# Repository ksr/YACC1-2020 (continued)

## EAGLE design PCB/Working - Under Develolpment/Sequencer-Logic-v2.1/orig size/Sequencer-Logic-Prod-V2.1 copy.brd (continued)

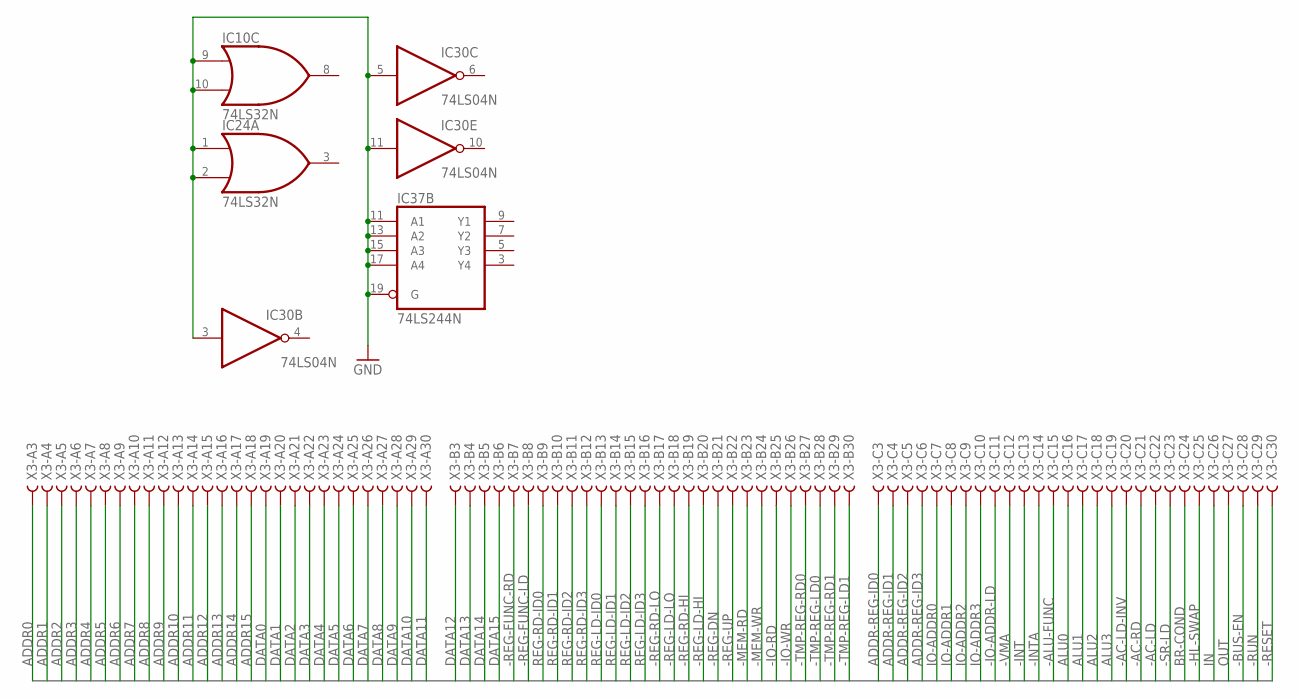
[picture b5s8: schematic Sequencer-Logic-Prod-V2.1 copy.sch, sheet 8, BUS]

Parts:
IC10, IC24: 74LS32N; DIL14
IC30: 74LS04N; DIL14
IC37: 74LS244N; DIL20
X3: FABC96R

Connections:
-AC-LD: X3.C22; also elsewhere on the board
-AC-LD-INV: X3.C20; also elsewhere on the board
-AC-RD: X3.C21; also elsewhere on the board
-ALU-FUNC: X3.C15; also elsewhere on the board
-BUS-EN: X3.C28; also elsewhere on the board
-HL-SWAP: X3.C25; also elsewhere on the board
-INT: X3.C13; also elsewhere on the board
-INTA: X3.C14; also elsewhere on the board
-IO-ADDR-LD: X3.C11; also elsewhere on the board
-IO-RD: X3.B25; also elsewhere on the board
-IO-WR: X3.B26; also elsewhere on the board
-MEM-RD: X3.B23; also elsewhere on the board
-MEM-WR: X3.B24; also elsewhere on the board
-REG-DN: X3.B21; also elsewhere on the board
-REG-FUNC-LD: X3.B8; also elsewhere on the board
-REG-FUNC-RD: X3.B7; also elsewhere on the board
-REG-LD-HI: X3.B20; also elsewhere on the board
-REG-LD-LO: X3.B18; also elsewhere on the board
-REG-RD-HI: X3.B19; also elsewhere on the board
-REG-RD-LO: X3.B17; also elsewhere on the board
-REG-UP: X3.B22; also elsewhere on the board
-RESET: X3.C30; also elsewhere on the board
-RUN: X3.C29
-SR-LD: X3.C23; also elsewhere on the board
-TMP-REG-LD0: X3.B28; also elsewhere on the board
-TMP-REG-LD1: X3.B30; also elsewhere on the board
-TMP-REG-RD0: X3.B27; also elsewhere on the board
-TMP-REG-RD1: X3.B29; also elsewhere on the board
-VMA: X3.C12; also elsewhere on the board
ADDR0: X3.A3
ADDR1: X3.A4
ADDR2: X3.A5
ADDR3: X3.A6
ADDR4: X3.A7
ADDR5: X3.A8
ADDR6: X3.A9
ADDR7: X3.A10
ADDR8: X3.A11
ADDR9: X3.A12
ADDR10: X3.A13
ADDR11: X3.A14
ADDR12: X3.A15
ADDR13: X3.A16
ADDR14: X3.A17
ADDR15: X3.A18
ADDR-REG-ID0: X3.C3; also elsewhere on the board
ADDR-REG-ID1: X3.C4; also elsewhere on the board
ADDR-REG-ID2: X3.C5; also elsewhere on the board
ADDR-REG-ID3: X3.C6; also elsewhere on the board
ALU0: X3.C16; also elsewhere on the board
ALU1: X3.C17; also elsewhere on the board
ALU2: X3.C18; also elsewhere on the board
ALU3: X3.C19; also elsewhere on the board
BR-COND: X3.C24; also elsewhere on the board
DATA0: X3.A19; also elsewhere on the board
DATA1: X3.A20; also elsewhere on the board
DATA2: X3.A21; also elsewhere on the board
DATA3: X3.A22; also elsewhere on the board
DATA4: X3.A23; also elsewhere on the board
DATA5: X3.A24; also elsewhere on the board
DATA6: X3.A25; also elsewhere on the board
DATA7: X3.A26; also elsewhere on the board
DATA8: X3.A27; also elsewhere on the board
DATA9: X3.A28; also elsewhere on the board
DATA10: X3.A29; also elsewhere on the board
DATA11: X3.A30; also elsewhere on the board
DATA12: X3.B3; also elsewhere on the board
DATA13: X3.B4; also elsewhere on the board
DATA14: X3.B5; also elsewhere on the board
DATA15: X3.B6; also elsewhere on the board
GND: IC10.7 (GND), IC10.9 (I0), IC10.10 (I1), IC24.1 (I0), IC24.2 (I1), IC24.7 (GND), IC30.3 (I), IC30.5 (I), IC30.7 (GND), IC30.11 (I), IC37.10 (GND), IC37.11 (A1), IC37.13 (A2), IC37.15 (A3), IC37.17 (A4), IC37.19 (G); also elsewhere on the board
IN: X3.C26
IO-ADDR0: X3.C7; also elsewhere on the board
IO-ADDR1: X3.C8; also elsewhere on the board
IO-ADDR2: X3.C9; also elsewhere on the board
IO-ADDR3: X3.C10; also elsewhere on the board
OUT: X3.C27; also elsewhere on the board
REG-LD-ID0: X3.B13; also elsewhere on the board
REG-LD-ID1: X3.B14; also elsewhere on the board
REG-LD-ID2: X3.B15; also elsewhere on the board
REG-LD-ID3: X3.B16; also elsewhere on the board
REG-RD-ID0: X3.B9; also elsewhere on the board
REG-RD-ID1: X3.B10; also elsewhere on the board
REG-RD-ID2: X3.B11; also elsewhere on the board
REG-RD-ID3: X3.B12; also elsewhere on the board
VCC: IC10.14 (VCC), IC24.14 (VCC), IC30.14 (VCC), IC37.20 (VCC); also elsewhere on the board

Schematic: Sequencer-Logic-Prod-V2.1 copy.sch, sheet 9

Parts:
JP5: PINHD-2X2; 2X02
SV3, SV4: MA20-2

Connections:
-MEM-CPU-RESET: JP5.2; also elsewhere on the board
CADDR0: SV4.14; also elsewhere on the board
CADDR1: SV4.16; also elsewhere on the board
CADDR2: SV4.18; also elsewhere on the board
CADDR3: SV4.20; also elsewhere on the board
CADDR4: SV4.22; also elsewhere on the board
CADDR5: SV4.24; also elsewhere on the board
CADDR6: SV4.26; also elsewhere on the board
CADDR7: SV4.28; also elsewhere on the board
CADDR8: SV4.30; also elsewhere on the board
CADDR9: SV4.32; also elsewhere on the board
CADDR10: SV4.34; also elsewhere on the board
CADDR11: SV4.36; also elsewhere on the board
CADDR12: SV4.38; also elsewhere on the board
CADDR13: SV4.2; also elsewhere on the board
GND: SV4.39, SV4.40; also elsewhere on the board
READY: SV4.12; also elsewhere on the board
U-2-BYTE-OPERAND-SEL: SV4.10; also elsewhere on the board
U-AC-LD: SV4.7; also elsewhere on the board
U-AC-LD-INV: SV4.3; also elsewhere on the board
U-AC-RD: SV4.5; also elsewhere on the board
U-ALU-FUNC: SV3.34; also elsewhere on the board
U-BRANCH-RD: SV4.35; also elsewhere on the board
U-HL-SWAP: SV4.13; also elsewhere on the board
U-INT-JMP: SV4.6; also elsewhere on the board
U-INTA: SV4.19; also elsewhere on the board
U-IO-ADDR-LD: SV3.30; also elsewhere on the board
U-IO-RD: SV3.39; also elsewhere on the board
U-IO-WR: SV3.4; also elsewhere on the board
U-MEM-RD: SV3.35; also elsewhere on the board
U-MEM-WR: SV3.37; also elsewhere on the board
U-REG-DN: SV3.31; also elsewhere on the board
U-REG-FUNC-LD: SV3.5; also elsewhere on the board
U-REG-FUNC-RD: SV3.3; also elsewhere on the board
U-REG-RD-HI: SV3.27; also elsewhere on the board
U-REG-RD-LO: SV3.23; also elsewhere on the board
U-REG-UP: SV3.33; also elsewhere on the board
U-SR-LD: SV4.9; also elsewhere on the board
U-TMP-REG-LD0: SV3.8; also elsewhere on the board
U-TMP-REG-LD1: SV3.12; also elsewhere on the board
U-TMP-REG-RD0: SV3.6; also elsewhere on the board
U-TMP-REG-RD1: SV3.10; also elsewhere on the board
U-VMA: SV3.32; also elsewhere on the board
UADDR-REG-ID0: SV3.14; also elsewhere on the board
UADDR-REG-ID1: SV3.16; also elsewhere on the board
UADDR-REG-ID2: SV3.18; also elsewhere on the board
UADDR-REG-ID3: SV3.20; also elsewhere on the board
UALU0: SV3.36; also elsewhere on the board
UALU1: SV3.38; also elsewhere on the board
UALU2: SV3.40; also elsewhere on the board
UALU3: SV4.1; also elsewhere on the board
UBR-TEST: SV4.11; also elsewhere on the board
UBRANCH-LD-HI: SV4.4; also elsewhere on the board
UBRANCH-LD-LO: SV4.37; also elsewhere on the board
UDEST-ADDR: JP5.4; also elsewhere on the board
UINT-EN: SV4.27; also elsewhere on the board
UINT-LD-HI: SV4.23; also elsewhere on the board
UINT-LD-LO: SV4.21; also elsewhere on the board
UINT-START: SV4.25; also elsewhere on the board
UIO-ADDR0: SV3.22; also elsewhere on the board
UIO-ADDR1: SV3.24; also elsewhere on the board
UIO-ADDR2: SV3.26; also elsewhere on the board
UIO-ADDR3: SV3.28; also elsewhere on the board
ULD-INS-REG: SV4.29; also elsewhere on the board
UOPERAND-CLK: SV4.33; also elsewhere on the board
UOUT-OFF: SV4.15; also elsewhere on the board
UOUT-ON: SV4.17; also elsewhere on the board
UREG-LD-HI: SV3.29; also elsewhere on the board
UREG-LD-ID0: SV3.15; also elsewhere on the board
UREG-LD-ID1: SV3.17; also elsewhere on the board
UREG-LD-ID2: SV3.19; also elsewhere on the board
UREG-LD-ID3: SV3.21; also elsewhere on the board
UREG-LD-LO: SV3.25; also elsewhere on the board
UREG-RD-ID0: SV3.7; also elsewhere on the board
UREG-RD-ID1: SV3.9; also elsewhere on the board
UREG-RD-ID2: SV3.11; also elsewhere on the board
UREG-RD-ID3: SV3.13; also elsewhere on the board
USOFT-HALT: SV4.8; also elsewhere on the board
USPARE3: JP5.1; also elsewhere on the board
USRC-ADDR: JP5.3; also elsewhere on the board
UUCODE-COUNT-RESET: SV4.31; also elsewhere on the board
VCC: SV3.1, SV3.2; also elsewhere on the board

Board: 4 copper layers, 100 parts (0 on the bottom side), 277 nets, no tracks yet.

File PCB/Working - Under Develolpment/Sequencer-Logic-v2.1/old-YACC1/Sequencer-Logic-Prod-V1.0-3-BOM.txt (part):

Partlist exported from /Users/ken/Library/Mobile Documents/com~apple~CloudDocs/YACC1A/Working/Sequencer-Logic-v1.0/Sequencer-Logic-Prod-V1.0-3.sch at 10/13/16 9:35 PM

Part     Value                     Device                    Package            Description                                                                                                                                                                                                                                                                                                                                                                                                                                                                                                                      MF MPN OC_FARNELL OC_NEWARK SPICEMODEL SPICEPREFIX
.        OUT                       LED5MM                    LED5MM             LED                                                                                                                                                                                                                                                                                                                                                                                                                                                                                                                                                                                
C1       .1                        CAPEZ                     CAP-PTH-SMALLEZ    Capacitor                                                                                                                                                                                                                                                                                                                                                                                                                                                                                                                                                                          
C2       .1                        CAPEZ                     CAP-PTH-SMALLEZ    Capacitor                                                                                                                                                                                                                                                                                                                                                                                                                                                                                                                                                                          
C3       .1                        CAPEZ                     CAP-PTH-SMALLEZ    Capacitor                                                                                                                                                                                                                                                                                                                                                                                                                                                                                                                                                                          
C4       .1                        CAPEZ                     CAP-PTH-SMALLEZ    Capacitor                                                                                                                                                                                                                                                                                                                                                                                                                                                                                                                                                                          
C5       .1                        CAPEZ                     CAP-PTH-SMALLEZ    Capacitor                                                                                                                                                                                                                                                                                                                                                                                                                                                                                                                                                                          
C6       .1                        CAPEZ                     CAP-PTH-SMALLEZ    Capacitor                                                                                                                                                                                                                                                                                                                                                                                                                                                                                                                                                                          
C7       .1                        CAPEZ                     CAP-PTH-SMALLEZ    Capacitor                                                                                                                                                                                                                                                                                                                                                                                                                                                                                                                                                                          
C8       .1                        CAPEZ                     CAP-PTH-SMALLEZ    Capacitor                                                                                                                                                                                                                                                                                                                                                                                                                                                                                                                                                                          
C9       .1                        CAPEZ                     CAP-PTH-SMALLEZ    Capacitor                                                                                                                                                                                                                                                                                                                                                                                                                                                                                                                                                                          
C10      .1                        CAPEZ                     CAP-PTH-SMALLEZ    Capacitor                                                                                                                                                                                                                                                                                                                                                                                                                                                                                                                                                                          
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
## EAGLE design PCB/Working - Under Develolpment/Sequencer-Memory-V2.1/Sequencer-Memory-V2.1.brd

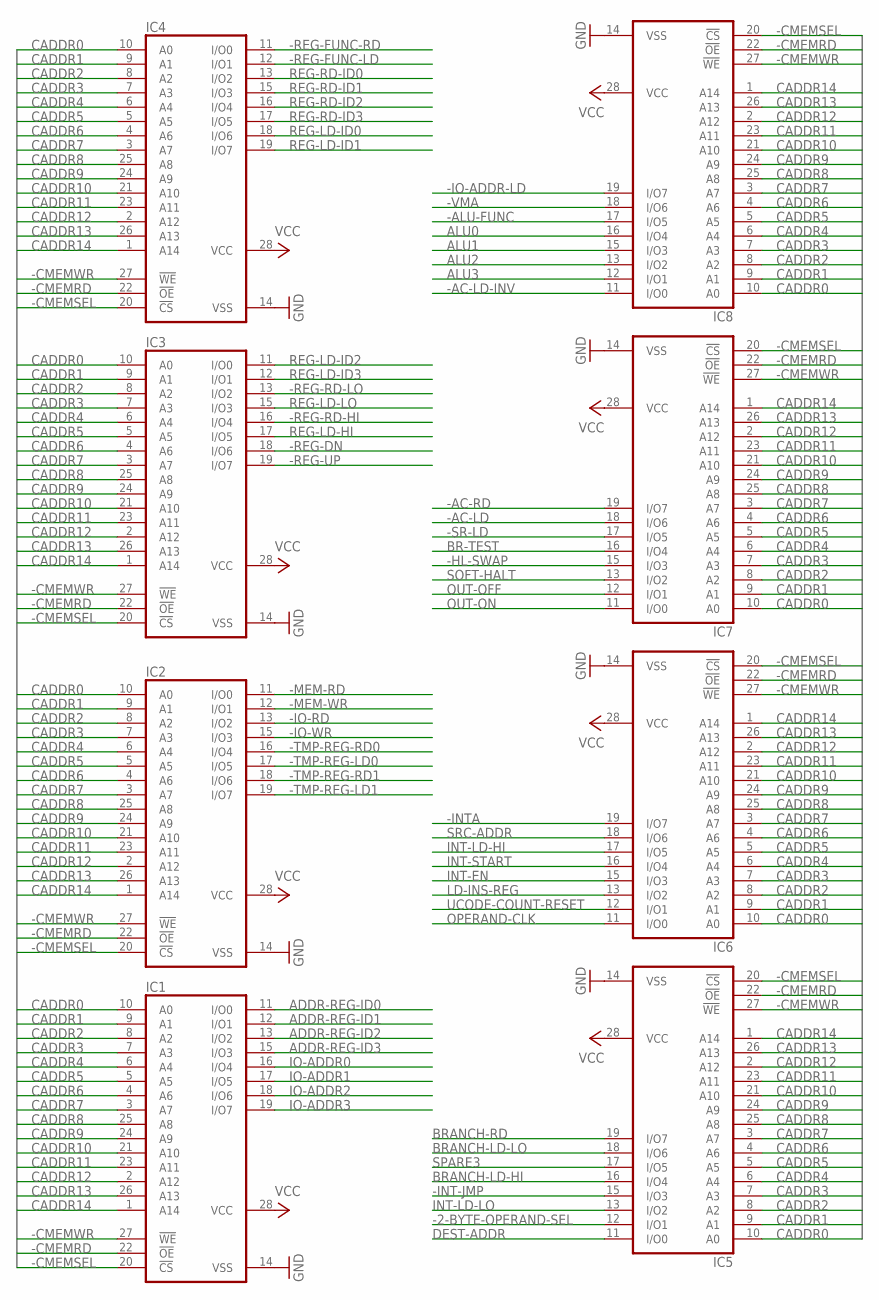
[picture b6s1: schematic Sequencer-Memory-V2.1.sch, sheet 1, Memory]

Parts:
IC1, IC2, IC3, IC4, IC5, IC6, IC7, IC8: 62256P; DIL28-6

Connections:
-2-BYTE-OPERAND-SEL: IC5.12 (I/O1); also elsewhere on the board
-AC-LD: IC7.18 (I/O6); also elsewhere on the board
-AC-LD-INV: IC8.11 (I/O0); also elsewhere on the board
-AC-RD: IC7.19 (I/O7); also elsewhere on the board
-ALU-FUNC: IC8.17 (I/O5); also elsewhere on the board
-CMEMRD: IC1.22 (!OE), IC2.22 (!OE), IC3.22 (!OE), IC4.22 (!OE), IC5.22 (!OE), IC6.22 (!OE), IC7.22 (!OE), IC8.22 (!OE); also elsewhere on the board
-CMEMSEL: IC1.20 (!CS), IC2.20 (!CS), IC3.20 (!CS), IC4.20 (!CS), IC5.20 (!CS), IC6.20 (!CS), IC7.20 (!CS), IC8.20 (!CS); also elsewhere on the board
-CMEMWR: IC1.27 (!WE), IC2.27 (!WE), IC3.27 (!WE), IC4.27 (!WE), IC5.27 (!WE), IC6.27 (!WE), IC7.27 (!WE), IC8.27 (!WE); also elsewhere on the board
-HL-SWAP: IC7.15 (I/O3); also elsewhere on the board
-INT-JMP: IC5.15 (I/O3); also elsewhere on the board
-INTA: IC6.19 (I/O7); also elsewhere on the board
-IO-ADDR-LD: IC8.19 (I/O7); also elsewhere on the board
-IO-RD: IC2.13 (I/O2); also elsewhere on the board
-IO-WR: IC2.15 (I/O3); also elsewhere on the board
-MEM-RD: IC2.11 (I/O0); also elsewhere on the board
-MEM-WR: IC2.12 (I/O1); also elsewhere on the board
-REG-DN: IC3.18 (I/O6); also elsewhere on the board
-REG-FUNC-LD: IC4.12 (I/O1); also elsewhere on the board
-REG-FUNC-RD: IC4.11 (I/O0); also elsewhere on the board
-REG-RD-HI: IC3.16 (I/O4); also elsewhere on the board
-REG-RD-LO: IC3.13 (I/O2); also elsewhere on the board
-REG-UP: IC3.19 (I/O7); also elsewhere on the board
-SR-LD: IC7.17 (I/O5); also elsewhere on the board
-TMP-REG-LD0: IC2.17 (I/O5); also elsewhere on the board
-TMP-REG-LD1: IC2.19 (I/O7); also elsewhere on the board
-TMP-REG-RD0: IC2.16 (I/O4); also elsewhere on the board
-TMP-REG-RD1: IC2.18 (I/O6); also elsewhere on the board
-VMA: IC8.18 (I/O6); also elsewhere on the board
ADDR-REG-ID0: IC1.11 (I/O0); also elsewhere on the board
ADDR-REG-ID1: IC1.12 (I/O1); also elsewhere on the board
ADDR-REG-ID2: IC1.13 (I/O2); also elsewhere on the board
ADDR-REG-ID3: IC1.15 (I/O3); also elsewhere on the board
ALU0: IC8.16 (I/O4); also elsewhere on the board
ALU1: IC8.15 (I/O3); also elsewhere on the board
ALU2: IC8.13 (I/O2); also elsewhere on the board
ALU3: IC8.12 (I/O1); also elsewhere on the board
BR-TEST: IC7.16 (I/O4); also elsewhere on the board
BRANCH-LD-HI: IC5.16 (I/O4); also elsewhere on the board
BRANCH-LD-LO: IC5.18 (I/O6); also elsewhere on the board
BRANCH-RD: IC5.19 (I/O7); also elsewhere on the board
CADDR0: IC1.10 (A0), IC2.10 (A0), IC3.10 (A0), IC4.10 (A0), IC5.10 (A0), IC6.10 (A0), IC7.10 (A0), IC8.10 (A0); also elsewhere on the board
CADDR1: IC1.9 (A1), IC2.9 (A1), IC3.9 (A1), IC4.9 (A1), IC5.9 (A1), IC6.9 (A1), IC7.9 (A1), IC8.9 (A1); also elsewhere on the board
CADDR2: IC1.8 (A2), IC2.8 (A2), IC3.8 (A2), IC4.8 (A2), IC5.8 (A2), IC6.8 (A2), IC7.8 (A2), IC8.8 (A2); also elsewhere on the board
CADDR3: IC1.7 (A3), IC2.7 (A3), IC3.7 (A3), IC4.7 (A3), IC5.7 (A3), IC6.7 (A3), IC7.7 (A3), IC8.7 (A3); also elsewhere on the board
CADDR4: IC1.6 (A4), IC2.6 (A4), IC3.6 (A4), IC4.6 (A4), IC5.6 (A4), IC6.6 (A4), IC7.6 (A4), IC8.6 (A4); also elsewhere on the board
CADDR5: IC1.5 (A5), IC2.5 (A5), IC3.5 (A5), IC4.5 (A5), IC5.5 (A5), IC6.5 (A5), IC7.5 (A5), IC8.5 (A5); also elsewhere on the board
CADDR6: IC1.4 (A6), IC2.4 (A6), IC3.4 (A6), IC4.4 (A6), IC5.4 (A6), IC6.4 (A6), IC7.4 (A6), IC8.4 (A6); also elsewhere on the board
CADDR7: IC1.3 (A7), IC2.3 (A7), IC3.3 (A7), IC4.3 (A7), IC5.3 (A7), IC6.3 (A7), IC7.3 (A7), IC8.3 (A7); also elsewhere on the board
CADDR8: IC1.25 (A8), IC2.25 (A8), IC3.25 (A8), IC4.25 (A8), IC5.25 (A8), IC6.25 (A8), IC7.25 (A8), IC8.25 (A8); also elsewhere on the board
CADDR9: IC1.24 (A9), IC2.24 (A9), IC3.24 (A9), IC4.24 (A9), IC5.24 (A9), IC6.24 (A9), IC7.24 (A9), IC8.24 (A9); also elsewhere on the board
CADDR10: IC1.21 (A10), IC2.21 (A10), IC3.21 (A10), IC4.21 (A10), IC5.21 (A10), IC6.21 (A10), IC7.21 (A10), IC8.21 (A10); also elsewhere on the board
CADDR11: IC1.23 (A11), IC2.23 (A11), IC3.23 (A11), IC4.23 (A11), IC5.23 (A11), IC6.23 (A11), IC7.23 (A11), IC8.23 (A11); also elsewhere on the board
CADDR12: IC1.2 (A12), IC2.2 (A12), IC3.2 (A12), IC4.2 (A12), IC5.2 (A12), IC6.2 (A12), IC7.2 (A12), IC8.2 (A12); also elsewhere on the board
CADDR13: IC1.26 (A13), IC2.26 (A13), IC3.26 (A13), IC4.26 (A13), IC5.26 (A13), IC6.26 (A13), IC7.26 (A13), IC8.26 (A13); also elsewhere on the board
CADDR14: IC1.1 (A14), IC2.1 (A14), IC3.1 (A14), IC4.1 (A14), IC5.1 (A14), IC6.1 (A14), IC7.1 (A14), IC8.1 (A14); also elsewhere on the board
DEST-ADDR: IC5.11 (I/O0); also elsewhere on the board
GND: IC1.14 (VSS), IC2.14 (VSS), IC3.14 (VSS), IC4.14 (VSS), IC5.14 (VSS), IC6.14 (VSS), IC7.14 (VSS), IC8.14 (VSS); also elsewhere on the board
INT-EN: IC6.15 (I/O3); also elsewhere on the board
INT-LD-HI: IC6.17 (I/O5); also elsewhere on the board
INT-LD-LO: IC5.13 (I/O2); also elsewhere on the board
INT-START: IC6.16 (I/O4); also elsewhere on the board
IO-ADDR0: IC1.16 (I/O4); also elsewhere on the board
IO-ADDR1: IC1.17 (I/O5); also elsewhere on the board
IO-ADDR2: IC1.18 (I/O6); also elsewhere on the board
IO-ADDR3: IC1.19 (I/O7); also elsewhere on the board
LD-INS-REG: IC6.13 (I/O2); also elsewhere on the board
OPERAND-CLK: IC6.11 (I/O0); also elsewhere on the board
OUT-OFF: IC7.12 (I/O1); also elsewhere on the board
OUT-ON: IC7.11 (I/O0); also elsewhere on the board
REG-LD-HI: IC3.17 (I/O5); also elsewhere on the board
REG-LD-ID0: IC4.18 (I/O6); also elsewhere on the board
REG-LD-ID1: IC4.19 (I/O7); also elsewhere on the board
REG-LD-ID2: IC3.11 (I/O0); also elsewhere on the board
REG-LD-ID3: IC3.12 (I/O1); also elsewhere on the board
REG-LD-LO: IC3.15 (I/O3); also elsewhere on the board
REG-RD-ID0: IC4.13 (I/O2); also elsewhere on the board
REG-RD-ID1: IC4.15 (I/O3); also elsewhere on the board
REG-RD-ID2: IC4.16 (I/O4); also elsewhere on the board
REG-RD-ID3: IC4.17 (I/O5); also elsewhere on the board
SOFT-HALT: IC7.13 (I/O2); also elsewhere on the board
SPARE3: IC5.17 (I/O5); also elsewhere on the board
SRC-ADDR: IC6.18 (I/O6); also elsewhere on the board
UCODE-COUNT-RESET: IC6.12 (I/O1); also elsewhere on the board
VCC: IC1.28 (VCC), IC2.28 (VCC), IC3.28 (VCC), IC4.28 (VCC), IC5.28 (VCC), IC6.28 (VCC), IC7.28 (VCC), IC8.28 (VCC); also elsewhere on the board

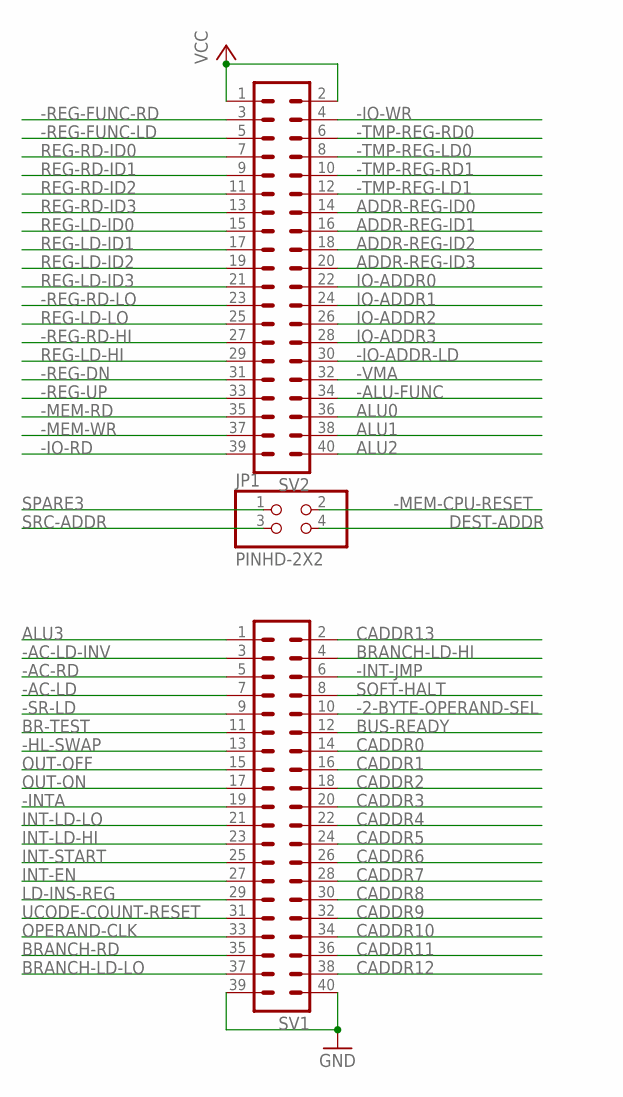
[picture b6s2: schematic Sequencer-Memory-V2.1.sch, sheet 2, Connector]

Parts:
JP1: PINHD-2X2; 2X02
SV1, SV2: MA20-2

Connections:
-2-BYTE-OPERAND-SEL: SV1.10; also elsewhere on the board
-AC-LD: SV1.7; also elsewhere on the board
-AC-LD-INV: SV1.3; also elsewhere on the board
-AC-RD: SV1.5; also elsewhere on the board
-ALU-FUNC: SV2.34; also elsewhere on the board
-HL-SWAP: SV1.13; also elsewhere on the board
-INT-JMP: SV1.6; also elsewhere on the board
-INTA: SV1.19; also elsewhere on the board
-IO-ADDR-LD: SV2.30; also elsewhere on the board
-IO-RD: SV2.39; also elsewhere on the board
-IO-WR: SV2.4; also elsewhere on the board
-MEM-CPU-RESET: JP1.2; also elsewhere on the board
-MEM-RD: SV2.35; also elsewhere on the board
-MEM-WR: SV2.37; also elsewhere on the board
-REG-DN: SV2.31; also elsewhere on the board
-REG-FUNC-LD: SV2.5; also elsewhere on the board
-REG-FUNC-RD: SV2.3; also elsewhere on the board
-REG-RD-HI: SV2.27; also elsewhere on the board
-REG-RD-LO: SV2.23; also elsewhere on the board
-REG-UP: SV2.33; also elsewhere on the board
-SR-LD: SV1.9; also elsewhere on the board
-TMP-REG-LD0: SV2.8; also elsewhere on the board
-TMP-REG-LD1: SV2.12; also elsewhere on the board
-TMP-REG-RD0: SV2.6; also elsewhere on the board
-TMP-REG-RD1: SV2.10; also elsewhere on the board
-VMA: SV2.32; also elsewhere on the board
ADDR-REG-ID0: SV2.14; also elsewhere on the board
ADDR-REG-ID1: SV2.16; also elsewhere on the board
ADDR-REG-ID2: SV2.18; also elsewhere on the board
ADDR-REG-ID3: SV2.20; also elsewhere on the board
ALU0: SV2.36; also elsewhere on the board
ALU1: SV2.38; also elsewhere on the board
ALU2: SV2.40; also elsewhere on the board
ALU3: SV1.1; also elsewhere on the board
BR-TEST: SV1.11; also elsewhere on the board
BRANCH-LD-HI: SV1.4; also elsewhere on the board
BRANCH-LD-LO: SV1.37; also elsewhere on the board
BRANCH-RD: SV1.35; also elsewhere on the board
BUS-READY: SV1.12; also elsewhere on the board
CADDR0: SV1.14; also elsewhere on the board
CADDR1: SV1.16; also elsewhere on the board
CADDR2: SV1.18; also elsewhere on the board
CADDR3: SV1.20; also elsewhere on the board
CADDR4: SV1.22; also elsewhere on the board
CADDR5: SV1.24; also elsewhere on the board
CADDR6: SV1.26; also elsewhere on the board
CADDR7: SV1.28; also elsewhere on the board
CADDR8: SV1.30; also elsewhere on the board
CADDR9: SV1.32; also elsewhere on the board
CADDR10: SV1.34; also elsewhere on the board
CADDR11: SV1.36; also elsewhere on the board
CADDR12: SV1.38; also elsewhere on the board
CADDR13: SV1.2; also elsewhere on the board
DEST-ADDR: JP1.4; also elsewhere on the board
GND: SV1.39, SV1.40; also elsewhere on the board
INT-EN: SV1.27; also elsewhere on the board
INT-LD-HI: SV1.23; also elsewhere on the board
INT-LD-LO: SV1.21; also elsewhere on the board
INT-START: SV1.25; also elsewhere on the board
IO-ADDR0: SV2.22; also elsewhere on the board
IO-ADDR1: SV2.24; also elsewhere on the board
IO-ADDR2: SV2.26; also elsewhere on the board
IO-ADDR3: SV2.28; also elsewhere on the board
LD-INS-REG: SV1.29; also elsewhere on the board
OPERAND-CLK: SV1.33; also elsewhere on the board
OUT-OFF: SV1.15; also elsewhere on the board
OUT-ON: SV1.17; also elsewhere on the board
REG-LD-HI: SV2.29; also elsewhere on the board
REG-LD-ID0: SV2.15; also elsewhere on the board
REG-LD-ID1: SV2.17; also elsewhere on the board
REG-LD-ID2: SV2.19; also elsewhere on the board
REG-LD-ID3: SV2.21; also elsewhere on the board
REG-LD-LO: SV2.25; also elsewhere on the board
REG-RD-ID0: SV2.7; also elsewhere on the board
REG-RD-ID1: SV2.9; also elsewhere on the board
REG-RD-ID2: SV2.11; also elsewhere on the board
REG-RD-ID3: SV2.13; also elsewhere on the board
SOFT-HALT: SV1.8; also elsewhere on the board
SPARE3: JP1.1; also elsewhere on the board
SRC-ADDR: JP1.3; also elsewhere on the board
UCODE-COUNT-RESET: SV1.31; also elsewhere on the board
VCC: SV2.1, SV2.2; also elsewhere on the board

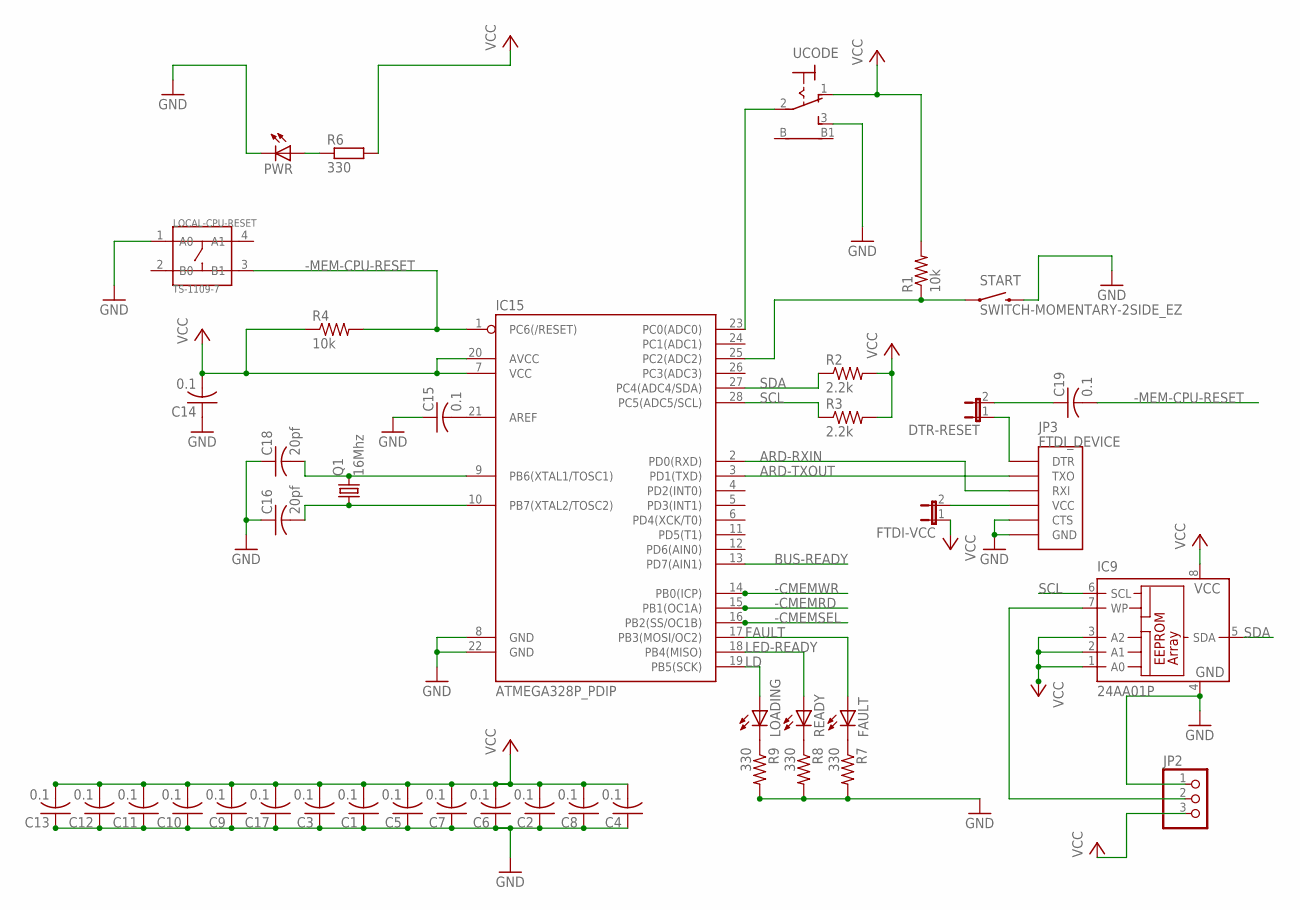
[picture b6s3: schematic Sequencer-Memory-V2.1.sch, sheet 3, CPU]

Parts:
C1, C2, C3, C4, C5, C6, C7, C8, C9, C10, C11, C12, C13, C14, C15, C17, C19: 0.1; C025-024X044
C16, C18: 20pf; C025-024X044
DTR-RESET: JP1E; JP1
FAULT: LED5MM
FTDI-VCC: JP1E; JP1
IC9: 24AA01P; DIL8
IC15: ATMEGA328P_PDIP; DIL28-3
JP2: PINHD-1X3; 1X03
JP3: FTDI_DEVICE; FTDI_DEVICE_SIDE
LOADING: LED5MM
LOCAL-CPU-RESET: TS-1109-7; SW4-6.2X6.2X5.0MM
PWR: LED5MM
Q1: 16Mhz; HC49/S
R1, R4: 10k; 0207/10
R2, R3: 2.2k; 0207/10
R6, R7, R8, R9: 330; 0207/10
READY: LED5MM
START: SWITCH-MOMENTARY-2SIDE_EZ; TACTILE-PTH-SIDEEZ
UCODE: 9070-1W

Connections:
-CMEMRD: IC15.15 (PB1(OC1A)); also elsewhere on the board
-CMEMSEL: IC15.16 (PB2(SS/OC1B)); also elsewhere on the board
-CMEMWR: IC15.14 (PB0(ICP)); also elsewhere on the board
-MEM-CPU-RESET: C19.2, IC15.1 (PC6(/RESET)), LOCAL-CPU-RESET.3 (B1), R4.2; also elsewhere on the board
ARD-RXIN: IC15.2 (PD0(RXD)), JP3.P$3 (RXI)
ARD-TXOUT: IC15.3 (PD1(TXD)), JP3.P$2 (TXO)
BUS-READY: IC15.13 (PD7(AIN1)); also elsewhere on the board
FAULT: FAULT.A, IC15.17 (PB3(MOSI/OC2))
GND: C1.1, C2.1, C3.1, C4.1, C5.1, C6.1, C7.1, C8.1, C9.1, C10.1, C11.1, C12.1, C13.1, C14.1, C15.1, C16.1, C17.1, C18.1, IC9.4 (GND), IC15.8 (GND), IC15.22 (GND), JP2.1, JP3.P$5 (CTS), JP3.P$6 (GND), LOCAL-CPU-RESET.1 (A0), PWR.K (C), R7.2, R8.2, R9.2, START.2, UCODE.3 (S); also elsewhere on the board
LD: IC15.19 (PB5(SCK)), LOADING.A
LED-READY: IC15.18 (PB4(MISO)), READY.A
unnamed: PWR.A, R6.1
unnamed: C18.2, IC15.9 (PB6(XTAL1/TOSC1)), Q1.2
unnamed: C16.2, IC15.10 (PB7(XTAL2/TOSC2)), Q1.1
unnamed: C19.1, DTR-RESET.2
unnamed: C15.2, IC15.21 (AREF)
unnamed: R8.1, READY.K (C)
unnamed: LOADING.K (C), R9.1
unnamed: FAULT.K (C), R7.1
unnamed: IC15.23 (PC0(ADC0)), UCODE.2
unnamed: IC9.7 (WP), JP2.2
unnamed: DTR-RESET.1, JP3.P$1 (DTR)
unnamed: FTDI-VCC.2, JP3.P$4 (VCC)
unnamed: IC15.25 (PC2(ADC2)), R1.1, START.1
SCL: IC9.6 (SCL), IC15.28 (PC5(ADC5/SCL)), R3.1; also elsewhere on the board
SDA: IC9.5 (SDA), IC15.27 (PC4(ADC4/SDA)), R2.1; also elsewhere on the board
VCC: C1.2, C2.2, C3.2, C4.2, C5.2, C6.2, C7.2, C8.2, C9.2, C10.2, C11.2, C12.2, C13.2, C14.2, C17.2, FTDI-VCC.1, IC9.1 (A0), IC9.2 (A1), IC9.3 (A2), IC9.8 (VCC), IC15.7 (VCC), IC15.20 (AVCC), JP2.3, R1.2, R2.2, R3.2, R4.1, R6.2, UCODE.1 (O); also elsewhere on the board
